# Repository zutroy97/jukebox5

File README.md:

# A 1970s Jukebox, Reborn for AirPlay

My step-father bought a 1970s-era jukebox that, from what we can tell,
spent a number of years in service at a Waffle House. We cleaned it up and
gutted its electromechanical guts, original lighting, and speakers,
replacing them with an early-90s Sony receiver, 6x9 car speakers, a powered
subwoofer, and a Raspberry Pi running the fantastic
[shairport-sync](https://github.com/mikebrady/shairport-sync). The jukebox
is now an AirPlay speaker, reachable from any iPhone or Mac on the network.

It looked and sounded great — but the two 7-segment displays and the
12-button keypad were just sitting there dark, begging to be used again.
This repo is what's driving them: the same Pi now also runs the original
control panel, turning it into a "now playing" display and remote control
for a Mac running Music.app.

Play something over AirPlay from another room, and the panel picks it up
automatically: a rolling "songs played" counter ticks up on the original
3-digit display, and the jukebox's own numeric keypad lets you punch in a
3-digit code to queue a specific track from a shared playlist — the way the
machine worked when it actually took quarters. Two 14-segment alphanumeric
displays were added alongside the original panel to show artist, title, and
album as they scroll by, since the jukebox never had anything capable of
showing that on its own.

## How it fits together

```
 Mac (Music.app) ──AirPlay──▶ shairport-sync ──MQTT──▶ Raspberry Pi ──▶ panel hardware
       ▲                                                    │
       └──────────────── SSH / JavaScript for Automation ◀──┘
```

- **shairport-sync** receives the AirPlay stream and publishes track
  metadata and play/pause/stop events over MQTT.
- The Pi subscribes, drives the physical panel in real time, and turns
  keypad presses into playback commands — sent back to the Mac either over
  MQTT or directly via JavaScript for Automation over SSH, whichever proves
  more reliable at the time.
- A custom PCB and level shifter bridge the panel's original 5V shift-register
  and keypad-matrix electronics to the Pi's 3.3V GPIO, backed by a small
  Linux kernel driver that exposes the panel as a character device.

## What's in here

| Path | What it is |
|---|---|
| [`src/`](src) | The Python application: MQTT/AirPlay integration, keypad state machine, animated display rendering, playlist lookup |
| [`linux/jukeboxPanelModule/`](linux/jukeboxPanelModule) | Kernel driver exposing the panel over `/dev/jukebox_panel` (text) and `/dev/jukebox_panel_bin` (binary, segment-level) protocols |
| [`hardware/`](hardware) | KiCad schematics/PCB layouts for the panel driver board and level-shifter |
| [`systemd/`](systemd) | Boot-time services: autostart, and a config-fetch step that pulls settings from the Mac |
| [`docs/`](docs) | Wiring diagrams, deployment notes, and a from-scratch [functional specification](docs/SPECIFICATION.md) of the whole system's behavior |

## Notable bits

- **Runs on a read-only root filesystem.** The Pi is sandboxed with systemd
  (`ProtectSystem=strict`), so config changes happen by editing a file on the
  Mac, which the Pi fetches at boot — see [`docs/deployment.md`](docs/deployment.md).
- **Segment-by-segment reveal animations**, not just instant text writes —
  characters materialize one LED segment at a time on both the alphanumeric
  and 7-segment displays.
- **A real hardware protocol**, reverse-engineered and reimplemented: the
  panel's MM5450/MM5451 shift-register displays and matrix keypad are driven
  over a shared clock/data bus with no separate keypad wiring — see
  [`docs/SPECIFICATION.md`](docs/SPECIFICATION.md) for the full wire-level
  writeup.
- **Graceful degradation everywhere**: a lost MQTT connection, a Mac that's
  unreachable at boot, or a corrupt config file each fall back to a safe,
  visible state instead of crashing.

## Credit where it's due

None of this works without [shairport-sync](https://github.com/mikebrady/shairport-sync),
Mike Brady's open-source AirPlay audio receiver. It's what turns the Pi into
an AirPlay speaker in the first place, and its built-in MQTT metadata
publisher — track info and play/pause/stop events over MQTT — is the
signal this entire panel is built to react to. Everything in this repo is
downstream of that project.

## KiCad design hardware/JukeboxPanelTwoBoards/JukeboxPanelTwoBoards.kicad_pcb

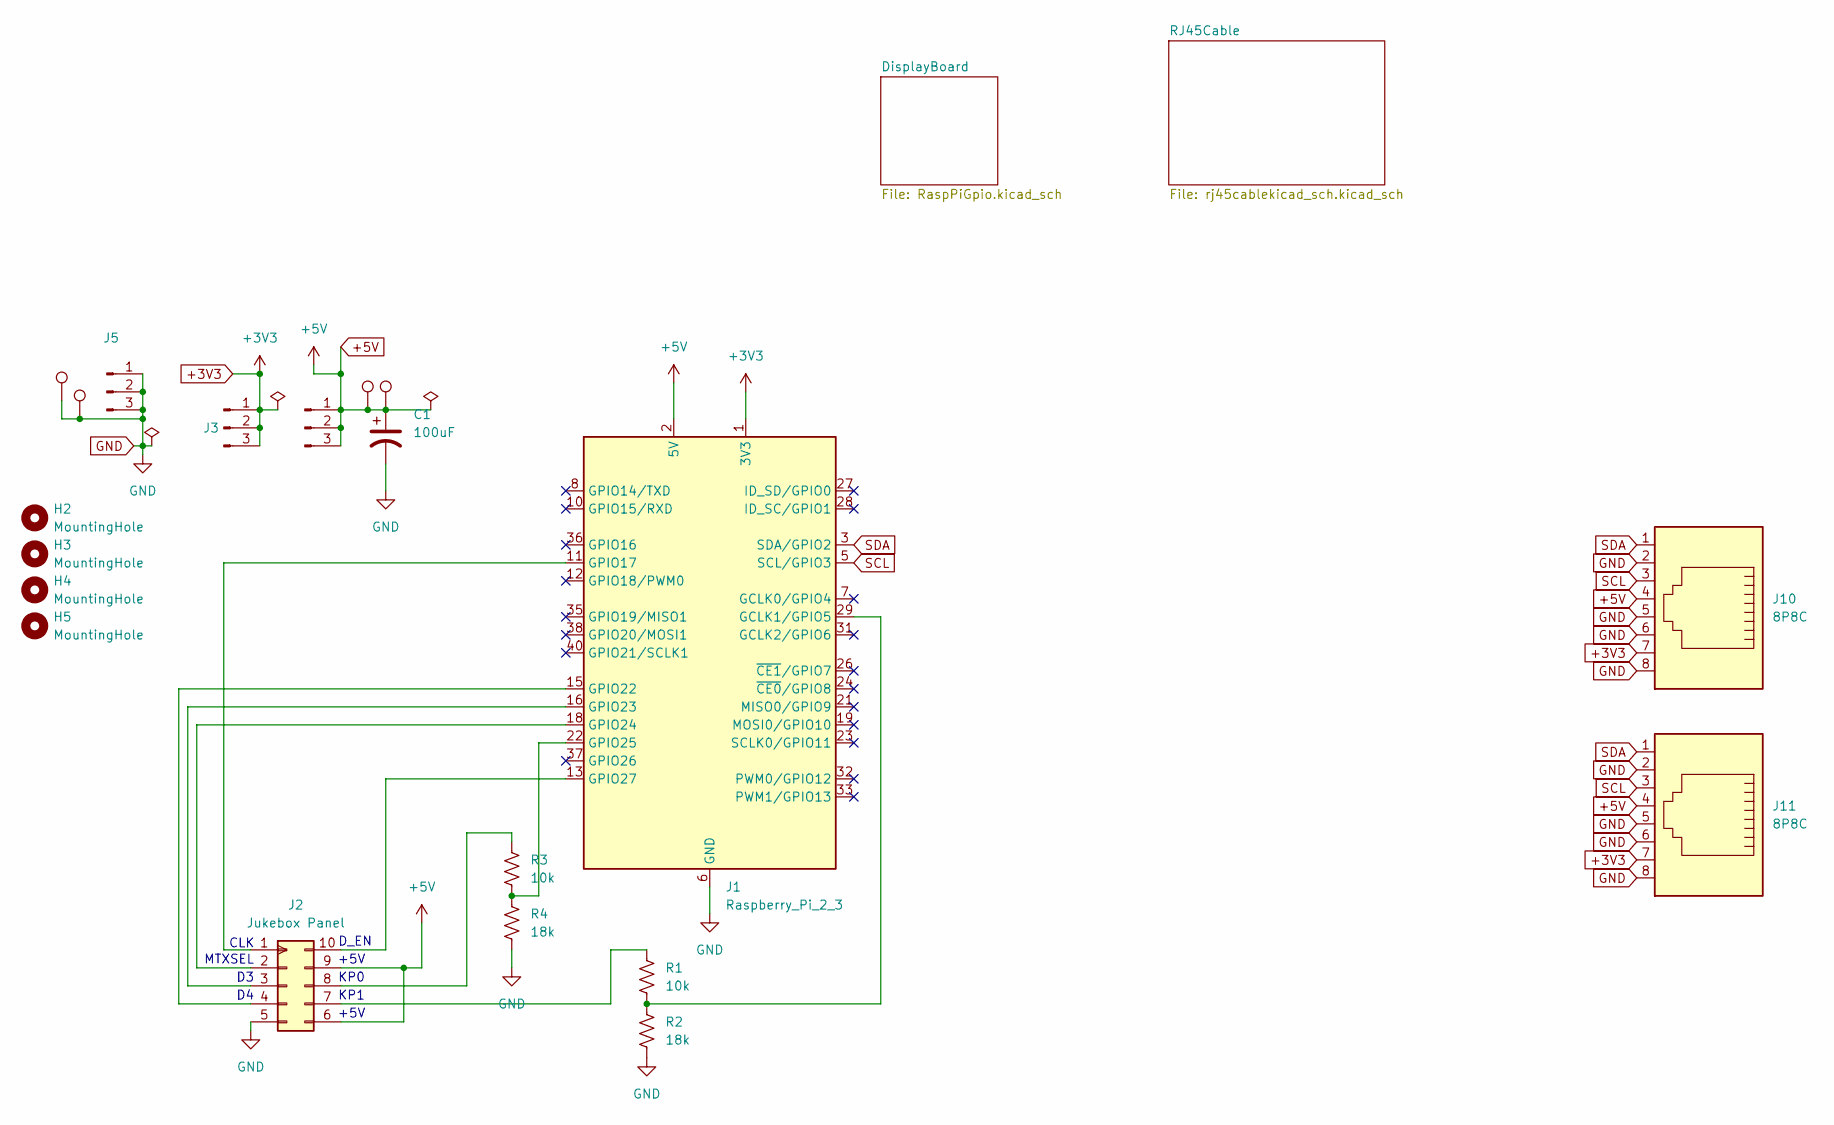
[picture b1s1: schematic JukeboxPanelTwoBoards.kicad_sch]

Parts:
C1: 100uF; CP_Radial_D4.0mm_P2.00mm
H2, H3, H4, H5: MountingHole; MountingHole_3.2mm_M3
J1: Raspberry_Pi_2_3; IDC-Header_2x20_P2.54mm_Horizontal
J2: Jukebox Panel; DIP-10_W7.62mm_Socket
J3: +3.3V; PinHeader_1x03_P2.54mm_Vertical
J4: +5V; PinHeader_1x03_P2.54mm_Vertical
J5: GND; PinHeader_1x03_P2.54mm_Vertical
J10, J11: 8P8C; RJ45_Ninigi_GE
R1, R3: 10k; R_Axial_DIN0204_L3.6mm_D1.6mm_P2.54mm_Vertical
R2, R4: 18k; R_Axial_DIN0204_L3.6mm_D1.6mm_P2.54mm_Vertical
TP_+5V1, TP_+5V2: TestPoint; TestPoint_THTPad_D2.5mm_Drill1.2mm
TP_GND2, TP_GND3: TestPoint; TestPoint_THTPad_D2.5mm_Drill1.2mm

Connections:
+3V3: J1.1 (3V3), J1.17 (3V3), J3.1, J3.2, J3.3, J10.7, J11.7; also elsewhere on the board
+5V: C1.1, J1.2 (5V), J1.4 (5V), J2.6 (Vdd1), J2.9 (Vdd2), J4.1, J4.2, J4.3, J10.4, J11.4, TP_+5V1.1 (1_1), TP_+5V2.1 (1_1); also elsewhere on the board
GND: C1.2, J1.6 (GND), J1.9 (GND), J1.14 (GND), J1.20 (GND), J1.25 (GND), J1.30 (GND), J1.34 (GND), J1.39 (GND), J2.5 (GND), J5.1, J5.2, J5.3, J10.2, J10.5, J10.6, J10.8, J11.2, J11.5, J11.6, J11.8, R2.2, R4.2, TP_GND2.1 (1_1), TP_GND3.1 (1_1); also elsewhere on the board
unnamed: J1.29 (GCLK1/GPIO5), R1.2, R2.1
unnamed: J1.11 (GPIO17), J2.1 (CLK)
unnamed: J1.15 (GPIO22), J2.4 (D4)
unnamed: J1.16 (GPIO23), J2.3 (D3)
unnamed: J1.18 (GPIO24), J2.2 (MTXSEL)
unnamed: J1.22 (GPIO25), R3.2, R4.1
unnamed: J1.13 (GPIO27), J2.10 (D_EN)
unnamed: J2.8 (KP0), R3.1
unnamed: J2.7 (KP1), R1.1
SCL: J1.5 (SCL/GPIO3), J10.3, J11.3; also elsewhere on the board
SDA: J1.3 (SDA/GPIO2), J10.1, J11.1; also elsewhere on the board

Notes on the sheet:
+5V
KP0
D_EN
KP1
MTXSEL
CLK

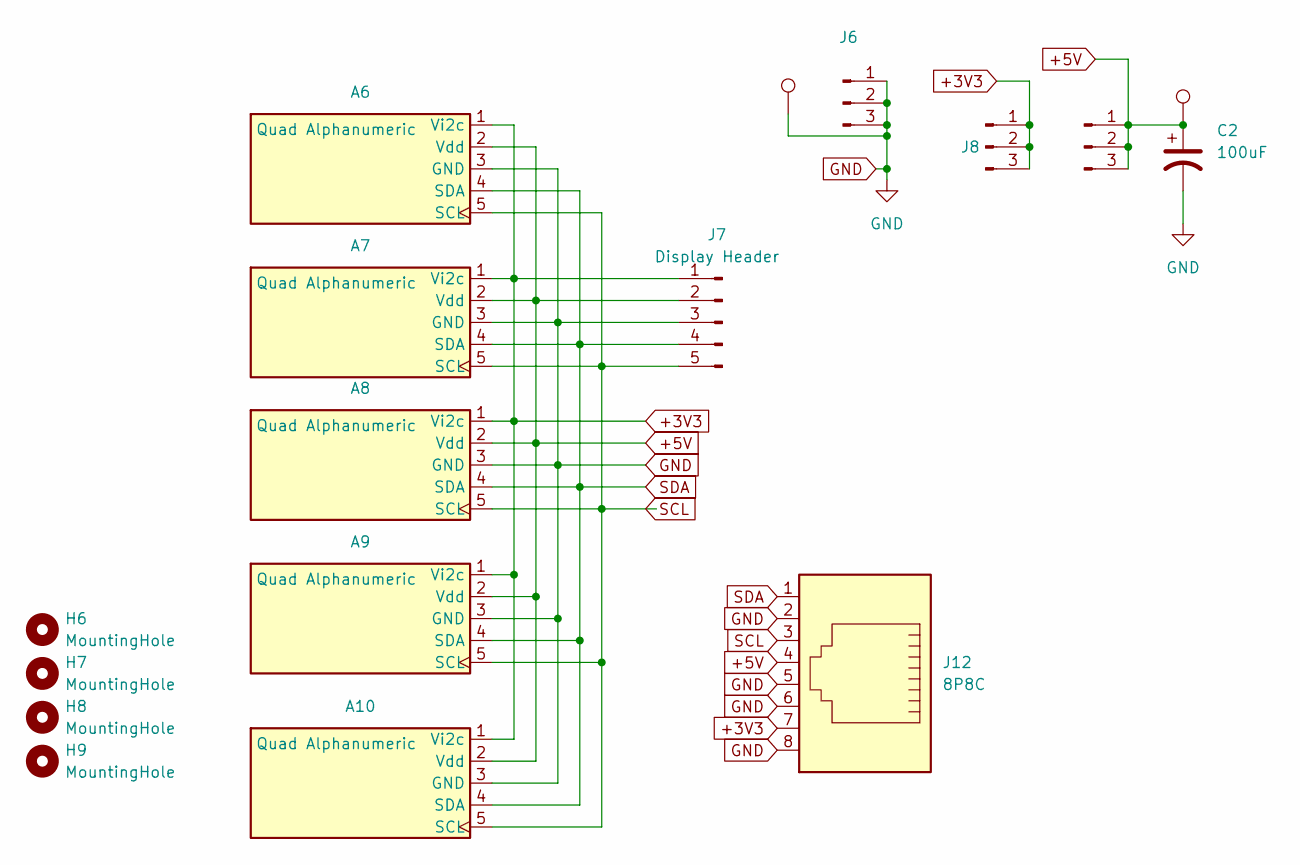
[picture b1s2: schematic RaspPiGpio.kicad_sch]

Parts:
A6, A7, A8, A9, A10: Quad Alphanumeric; Adafruit_1911_QuadAlphaNum
C2: 100uF; CP_Radial_D4.0mm_P2.00mm
H6, H7, H8, H9: MountingHole; MountingHole_3.2mm_M3
J6: GND; PinHeader_1x03_P2.54mm_Vertical
J7: Display Header; PinHeader_1x05_P2.54mm_Vertical
J8: +3.3V; PinHeader_1x03_P2.54mm_Vertical
J9: +5V; PinHeader_1x03_P2.54mm_Vertical
J12: 8P8C; RJ45_Ninigi_GE
TP_+5V3: TestPoint; TestPoint_THTPad_D2.5mm_Drill1.2mm
TP_GND4: TestPoint; TestPoint_THTPad_D2.5mm_Drill1.2mm

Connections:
+3V3: A6.1 (Vi2c), A7.1 (Vi2c), A8.1 (Vi2c), A9.1 (Vi2c), A10.1 (Vi2c), J7.1, J8.1, J8.2, J8.3, J12.7; also elsewhere on the board
+5V: A6.2 (Vdd), A7.2 (Vdd), A8.2 (Vdd), A9.2 (Vdd), A10.2 (Vdd), C2.1, J7.2, J9.1, J9.2, J9.3, J12.4, TP_+5V3.1 (1_1); also elsewhere on the board
GND: A6.3 (GND), A7.3 (GND), A8.3 (GND), A9.3 (GND), A10.3 (GND), C2.2, J6.1, J6.2, J6.3, J7.3, J12.2, J12.5, J12.6, J12.8, TP_GND4.1 (1_1); also elsewhere on the board
SCL: A6.5 (SCL), A7.5 (SCL), A8.5 (SCL), A9.5 (SCL), A10.5 (SCL), J7.5, J12.3; also elsewhere on the board
SDA: A6.4 (SDA), A7.4 (SDA), A8.4 (SDA), A9.4 (SDA), A10.4 (SDA), J7.4, J12.1; also elsewhere on the board

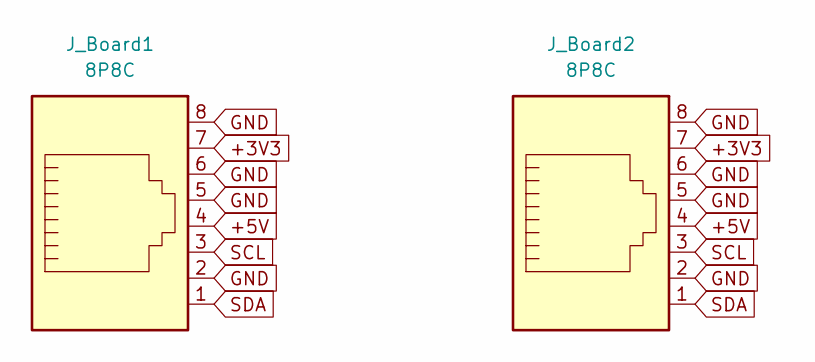
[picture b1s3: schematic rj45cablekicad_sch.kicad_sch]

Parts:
J_Board1, J_Board2: 8P8C; RJ45_Ninigi_GE

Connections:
unnamed: J_Board1.1, J_Board2.1
unnamed: J_Board1.2, J_Board1.5, J_Board1.6, J_Board1.8, J_Board2.2, J_Board2.5, J_Board2.6, J_Board2.8
unnamed: J_Board1.3, J_Board2.3
unnamed: J_Board1.4, J_Board2.4
unnamed: J_Board1.7, J_Board2.7

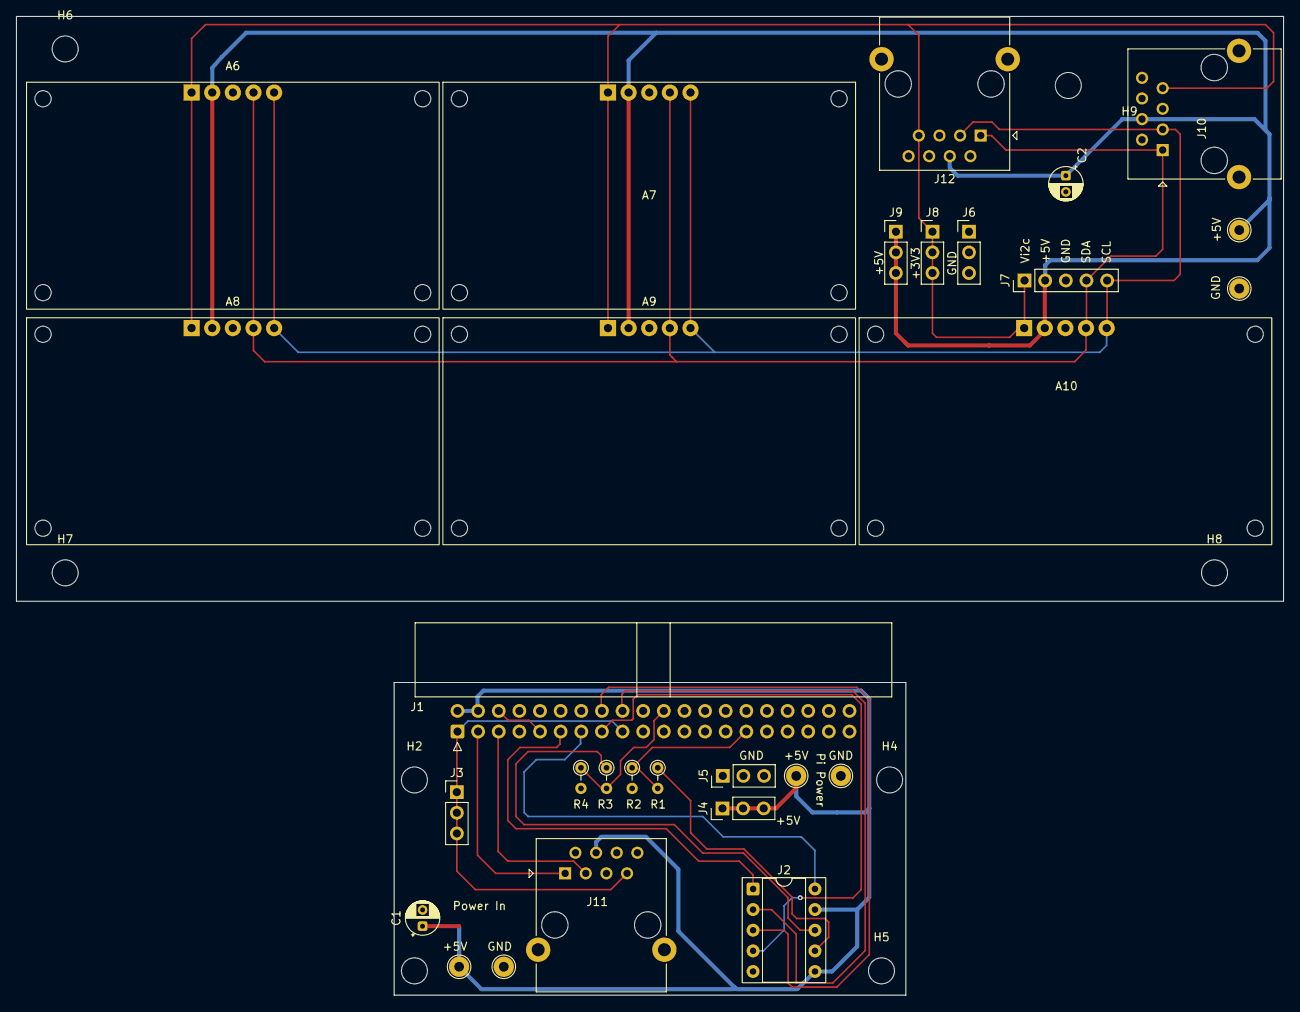
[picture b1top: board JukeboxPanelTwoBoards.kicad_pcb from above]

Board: 2 copper layers, 156.0 x 120.5 mm, 37 parts (0 on the bottom side), 14 nets.

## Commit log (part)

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2026-04-30 Added TextDiff
2026-04-30 need to reboot
2026-05-01 reorg of packages
2026-05-02 chainlink
2026-05-16 updated requirements
2026-05-16 Test using Task Group
2026-05-16 Clean up main
2026-05-16 added basic coordinators
2026-05-16 Animated Sungle Line Displays
2026-05-17 More options for single line animator
2026-05-17 Slide is now the default
2026-05-21 trying led16 animators
2026-05-23 i2c working?
2026-05-23 fixed animation pop error
2026-05-27 Refactor main function and observer management; implement shutdown handling and display clearing
2026-05-28 Refactor main function to streamline observer initialization and clean up commented code
2026-05-29 added single line animated simple
2026-05-30 more callbacks
2026-05-30 Added on_line_animation_finished
2026-05-30 added on_animation_finished
2026-05-30 Single sleep
2026-06-03 Refactor observers: replace SingleLineAnimatedSimpleObserver with SingleLineAnimatedObserverBase and update related imports
2026-06-10 Add LED16 animation support and refactor observers
    - Introduced AlienAnimator and LED16Static classes for LED16 display animations.
    - Added LED16TextAnimatorAdapter to integrate text animators with LED16.
    - Refactored observer classes: replaced SingleLineAnimatedObserverBase with SingleTextLineAnimatedObserver and SingleTextLineStaticObserver.
    - Updated observer states for better clarity and functionality.
    - Removed deprecated SingleLineObserver and simplified related logic.
2026-06-10 Refactor observers to use SingleLineLed16AnimatedObserver and update display handling
2026-06-14 Add Static text animator and enhance LED16 observers with clear functionality
2026-06-14 Implement clear display animations and refactor observer states
2026-06-21 added key/value observer
2026-06-27 Enhance observer functionality with timeout handling and animation state updates
2026-06-28 Update dependencies, add panel input/output classes, and implement song info update mechanism
2026-06-28 Clear animation (#2)
    * Implement clear display animations and refactor observer states
    * added key/value observer
    * Enhance observer functionality with timeout handling and animation state updates
    * Update dependencies, add panel input/output classes, and implement song info update mechanism
2026-06-28 Refactor async methods to synchronous in animation and observer classes
    - Changed async methods to synchronous in various animation classes including AbstractAnimator, AbstractClearTextAnimator, and others.
    - Updated corresponding calls to these methods throughout the codebase to maintain functionality.
    - Adjusted the main execution flow in main.py to remove asyncio and use standard time.sleep for delays.
    - Modified the Coordinator class to run its loop in a separate thread instead of using asyncio.
    - Ensured that all observer classes and their methods are now synchronous, improving compatibility with the new threading model.
